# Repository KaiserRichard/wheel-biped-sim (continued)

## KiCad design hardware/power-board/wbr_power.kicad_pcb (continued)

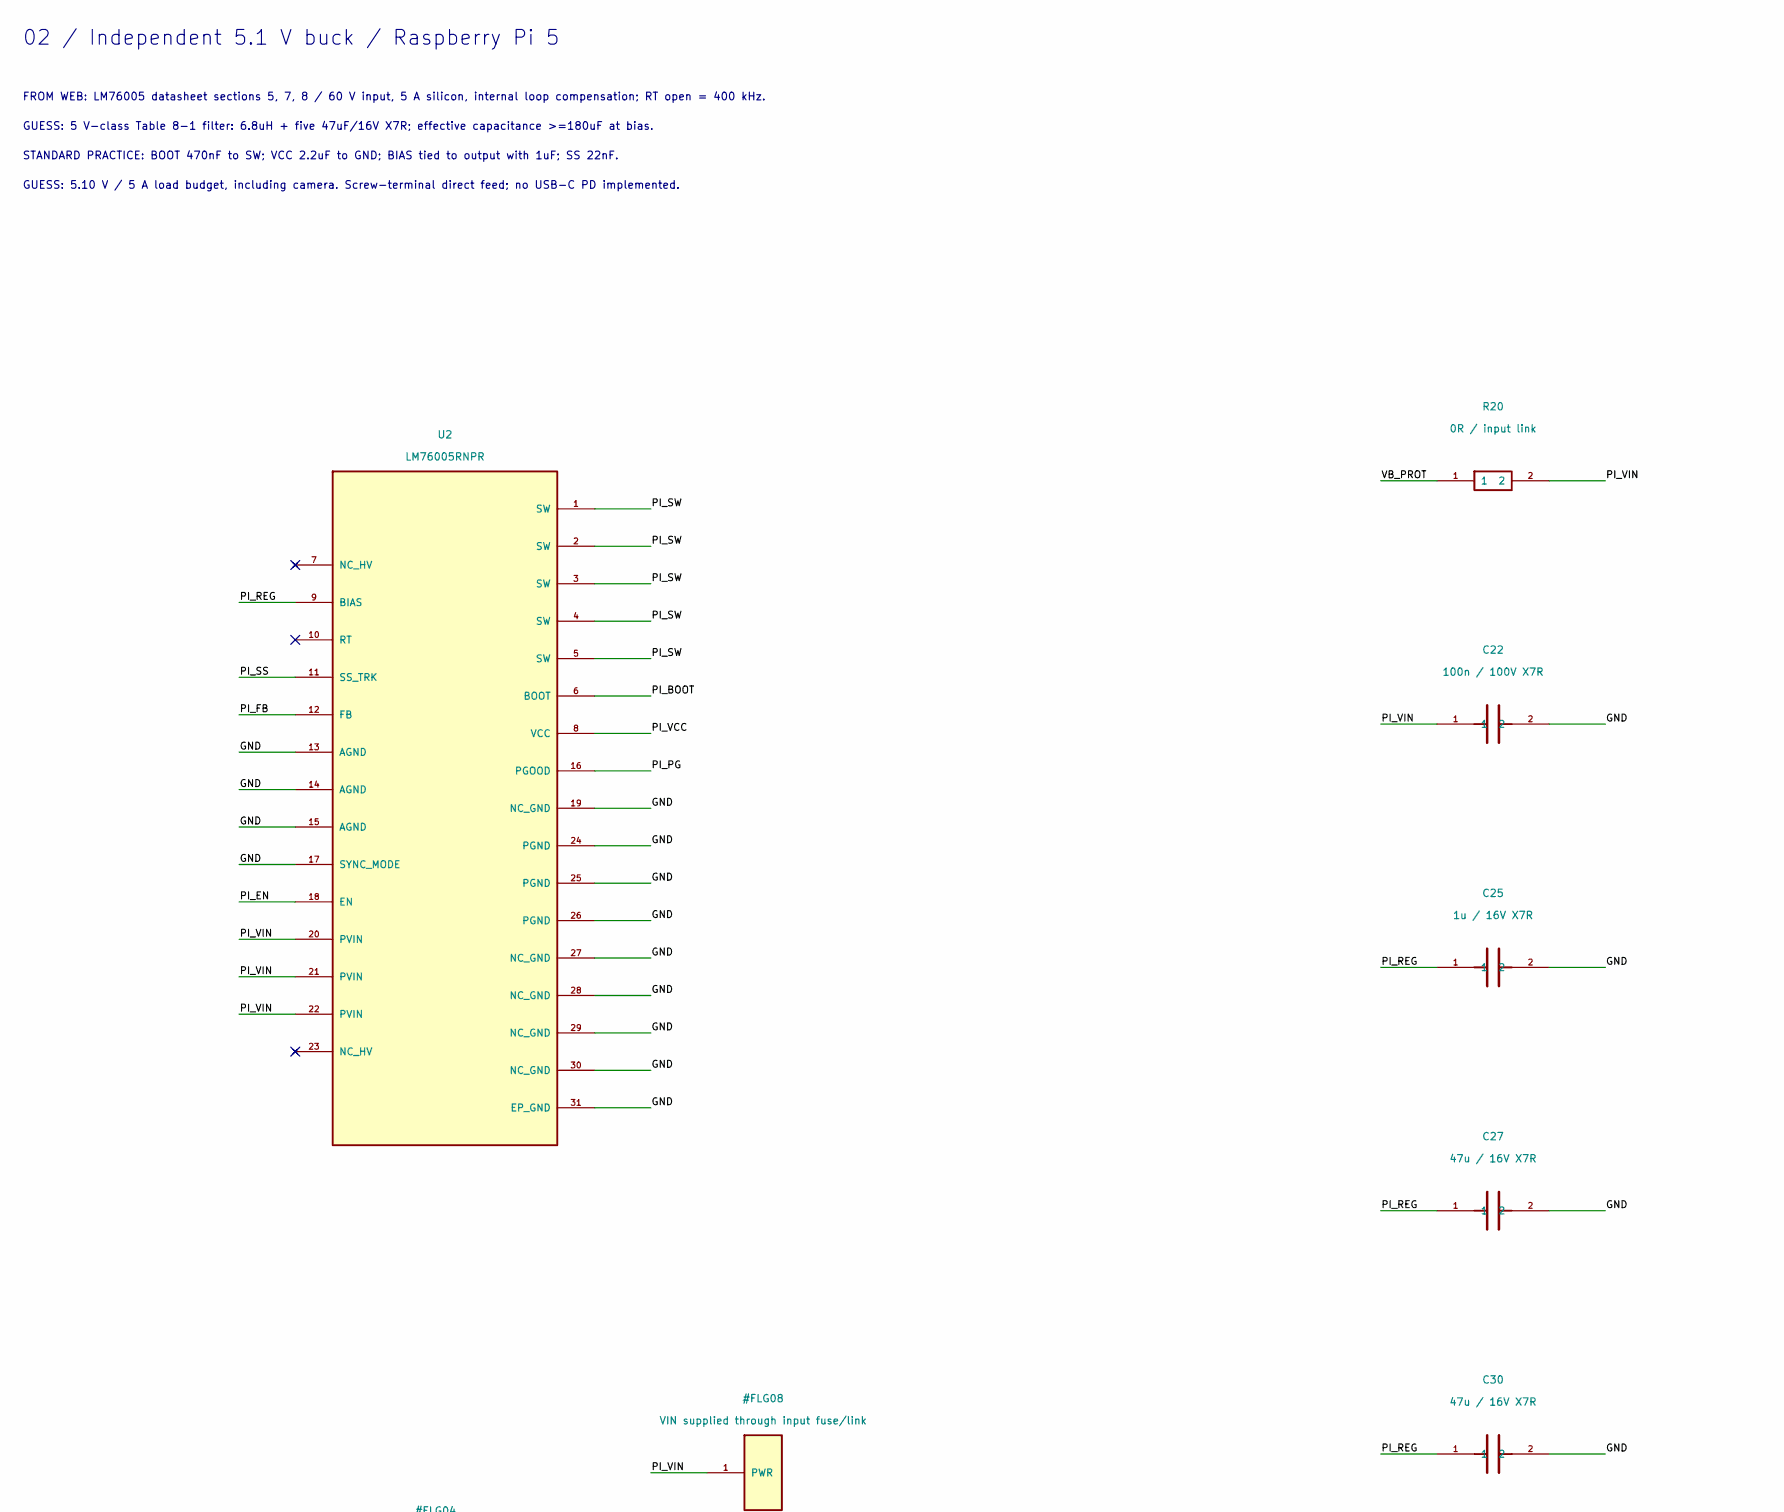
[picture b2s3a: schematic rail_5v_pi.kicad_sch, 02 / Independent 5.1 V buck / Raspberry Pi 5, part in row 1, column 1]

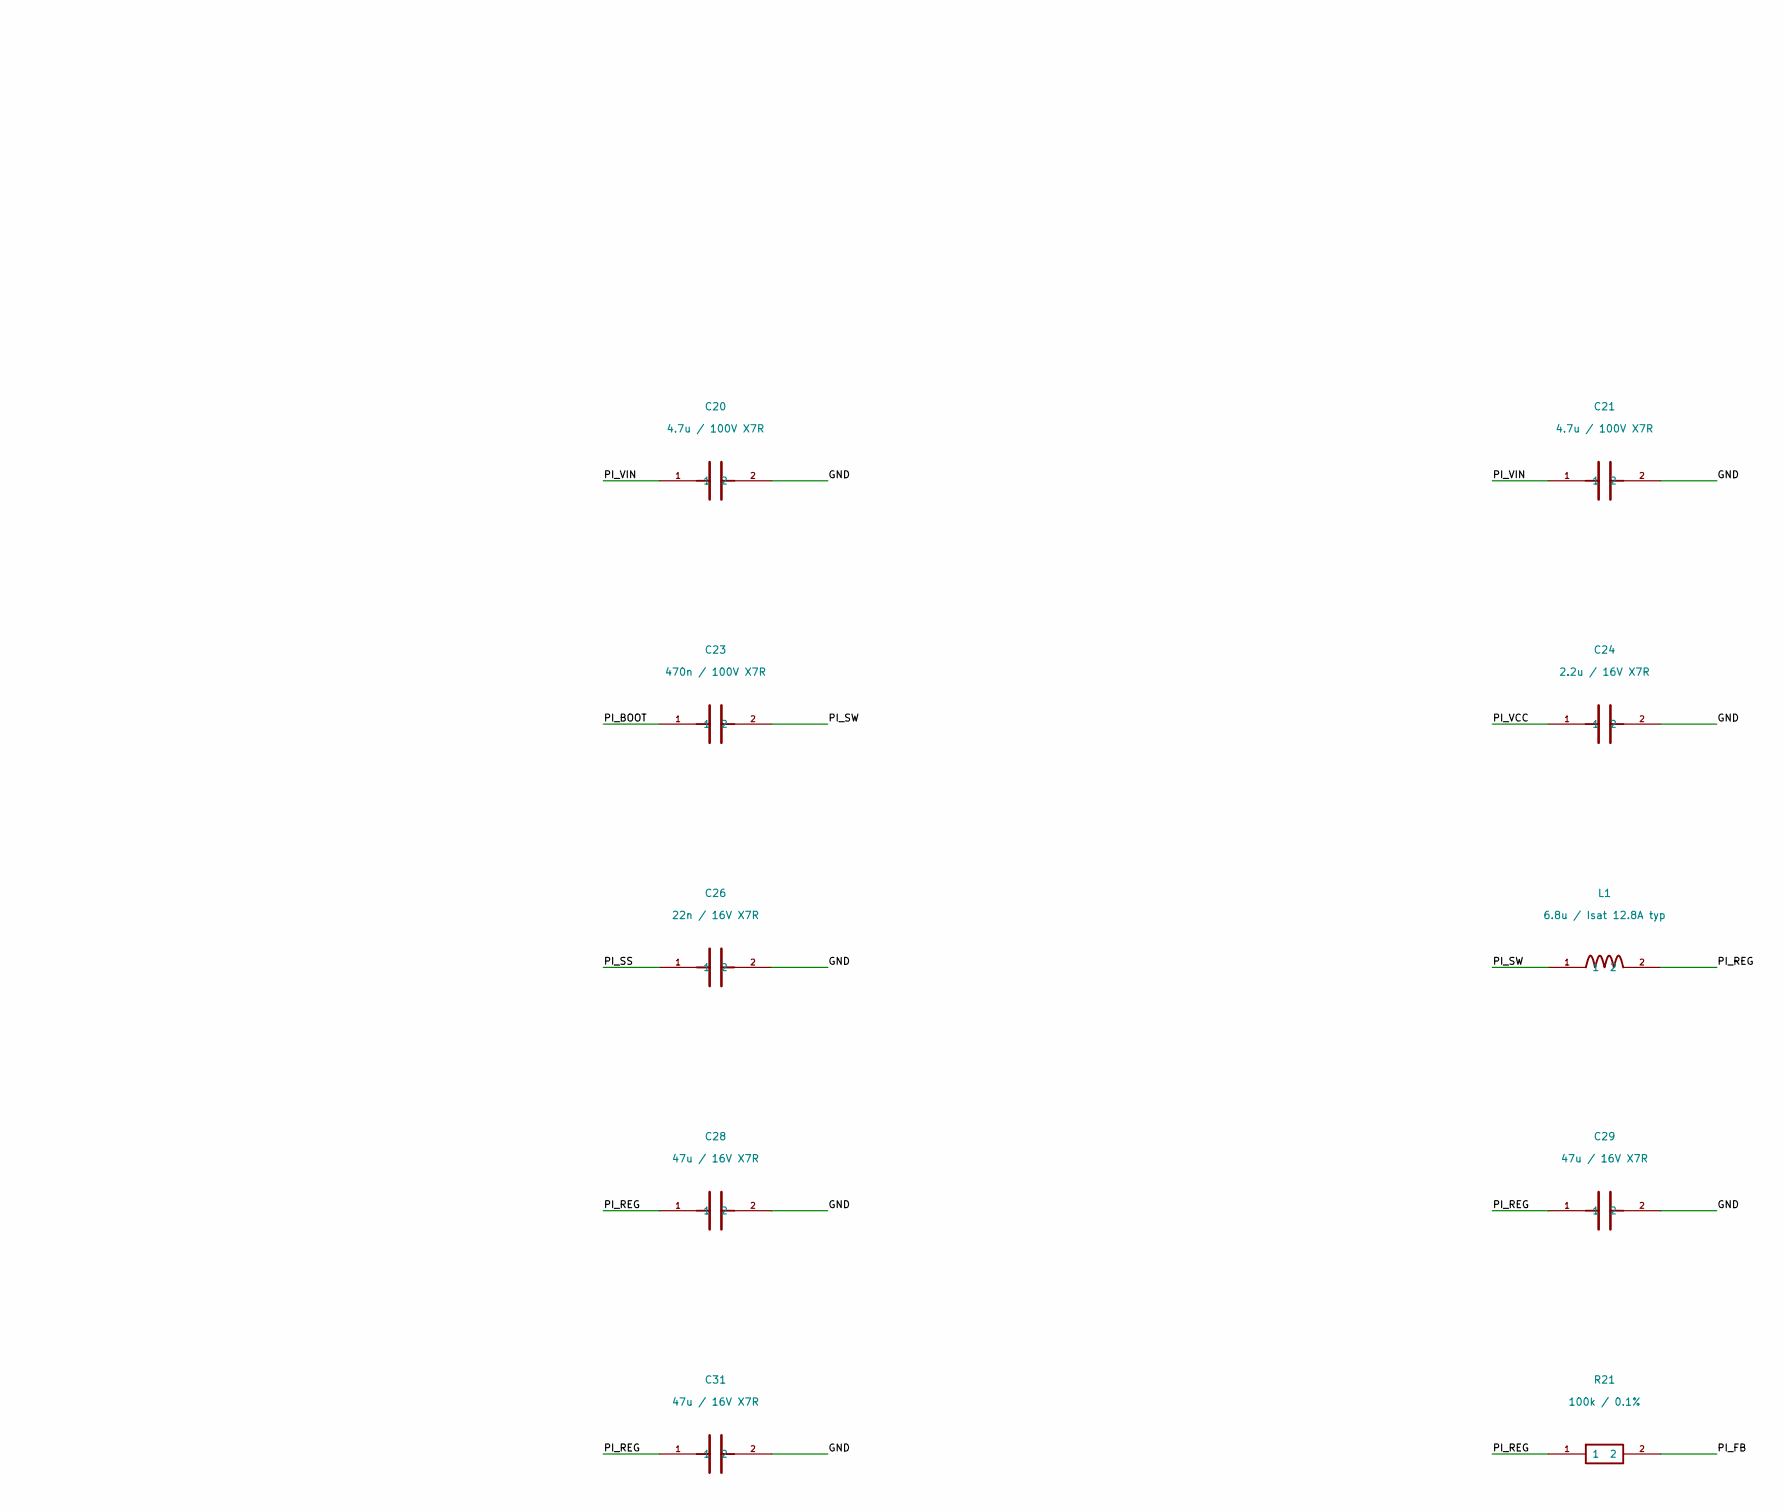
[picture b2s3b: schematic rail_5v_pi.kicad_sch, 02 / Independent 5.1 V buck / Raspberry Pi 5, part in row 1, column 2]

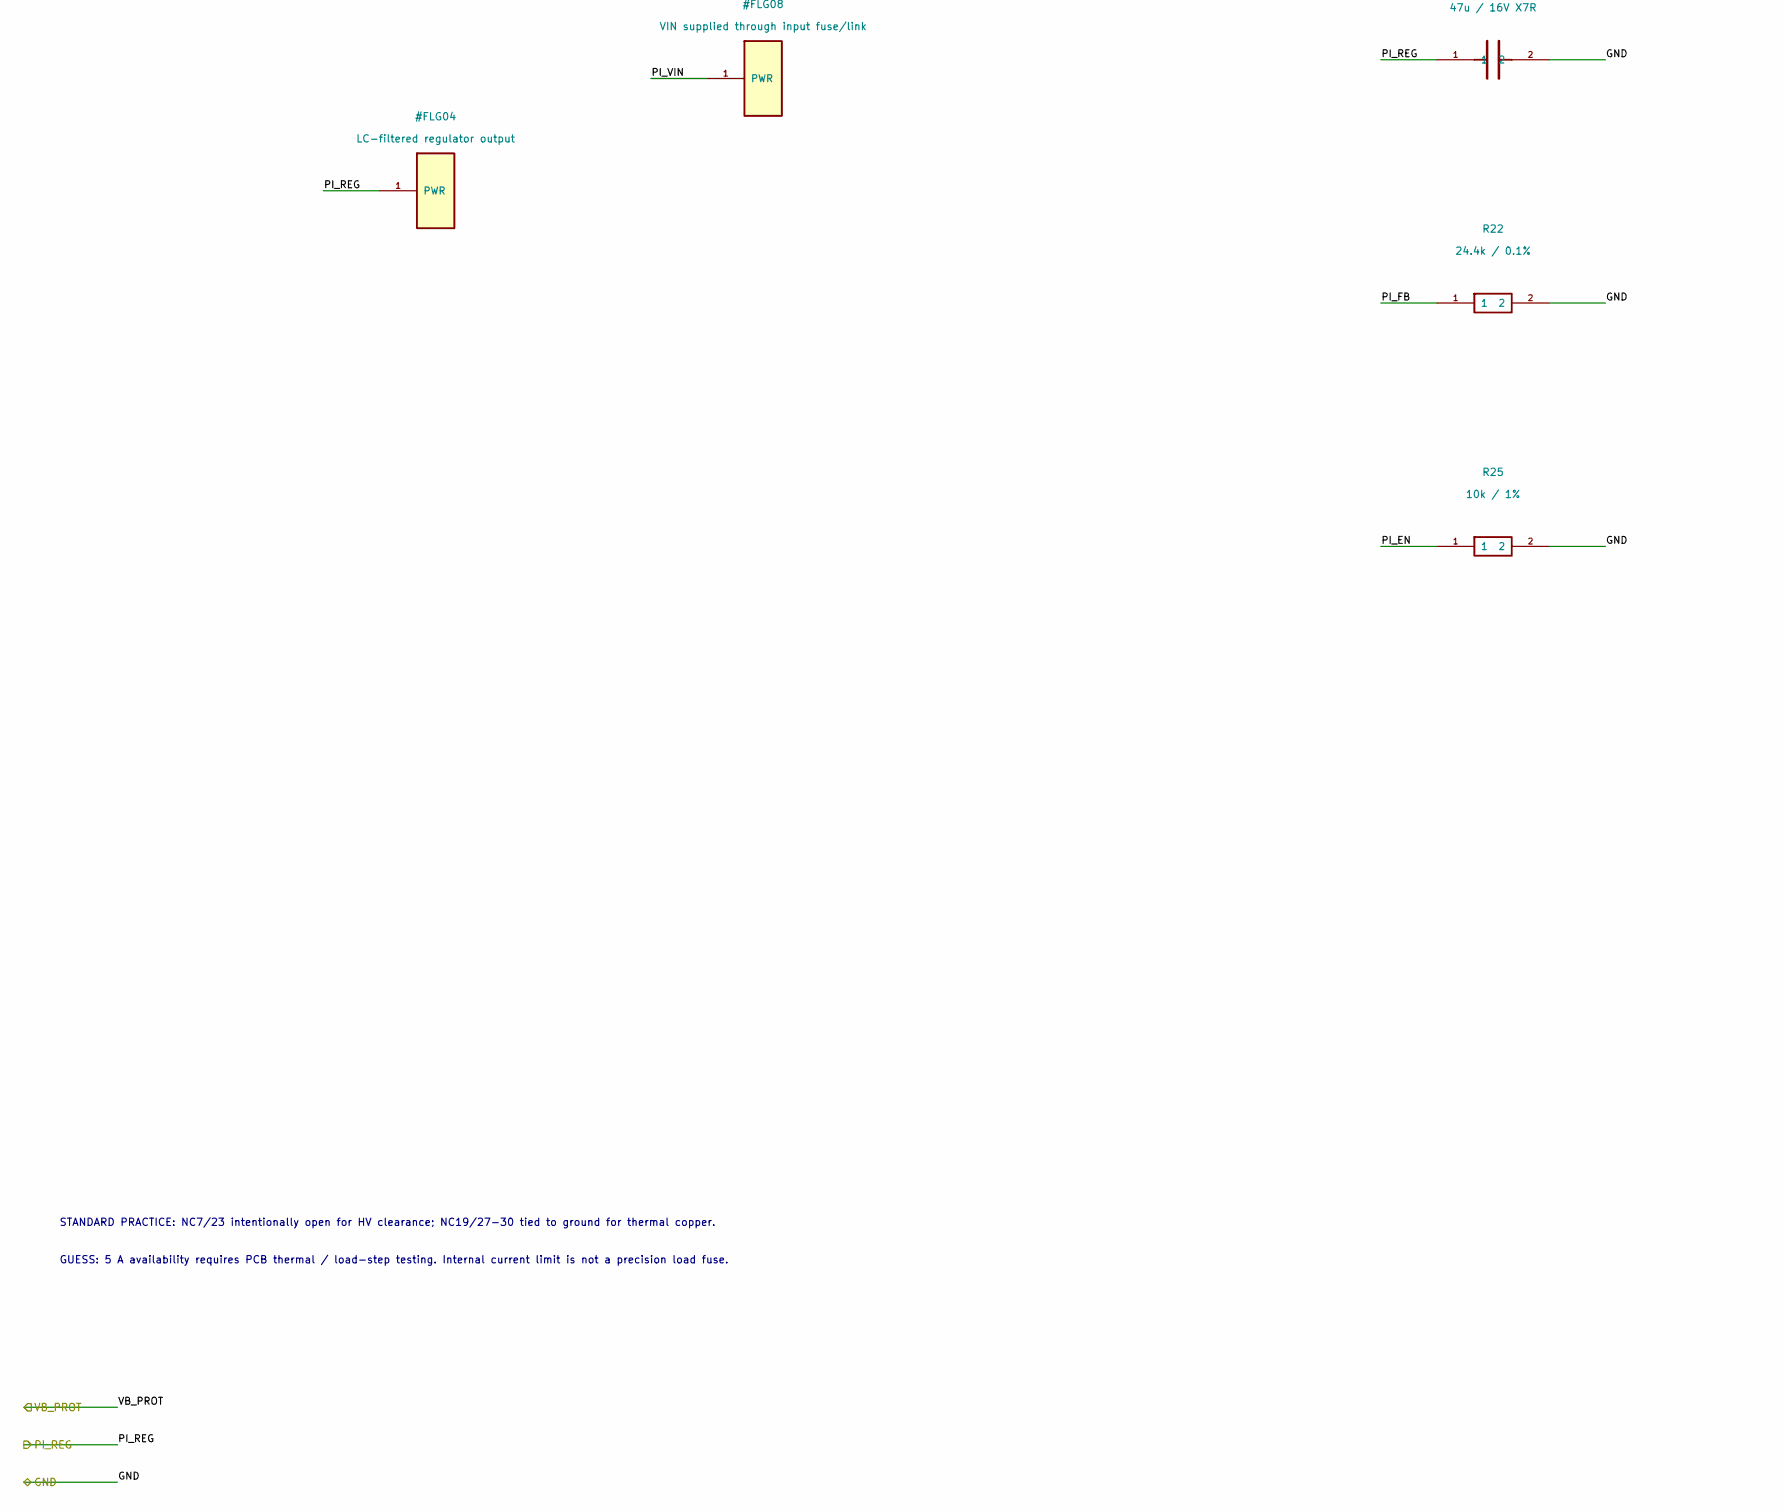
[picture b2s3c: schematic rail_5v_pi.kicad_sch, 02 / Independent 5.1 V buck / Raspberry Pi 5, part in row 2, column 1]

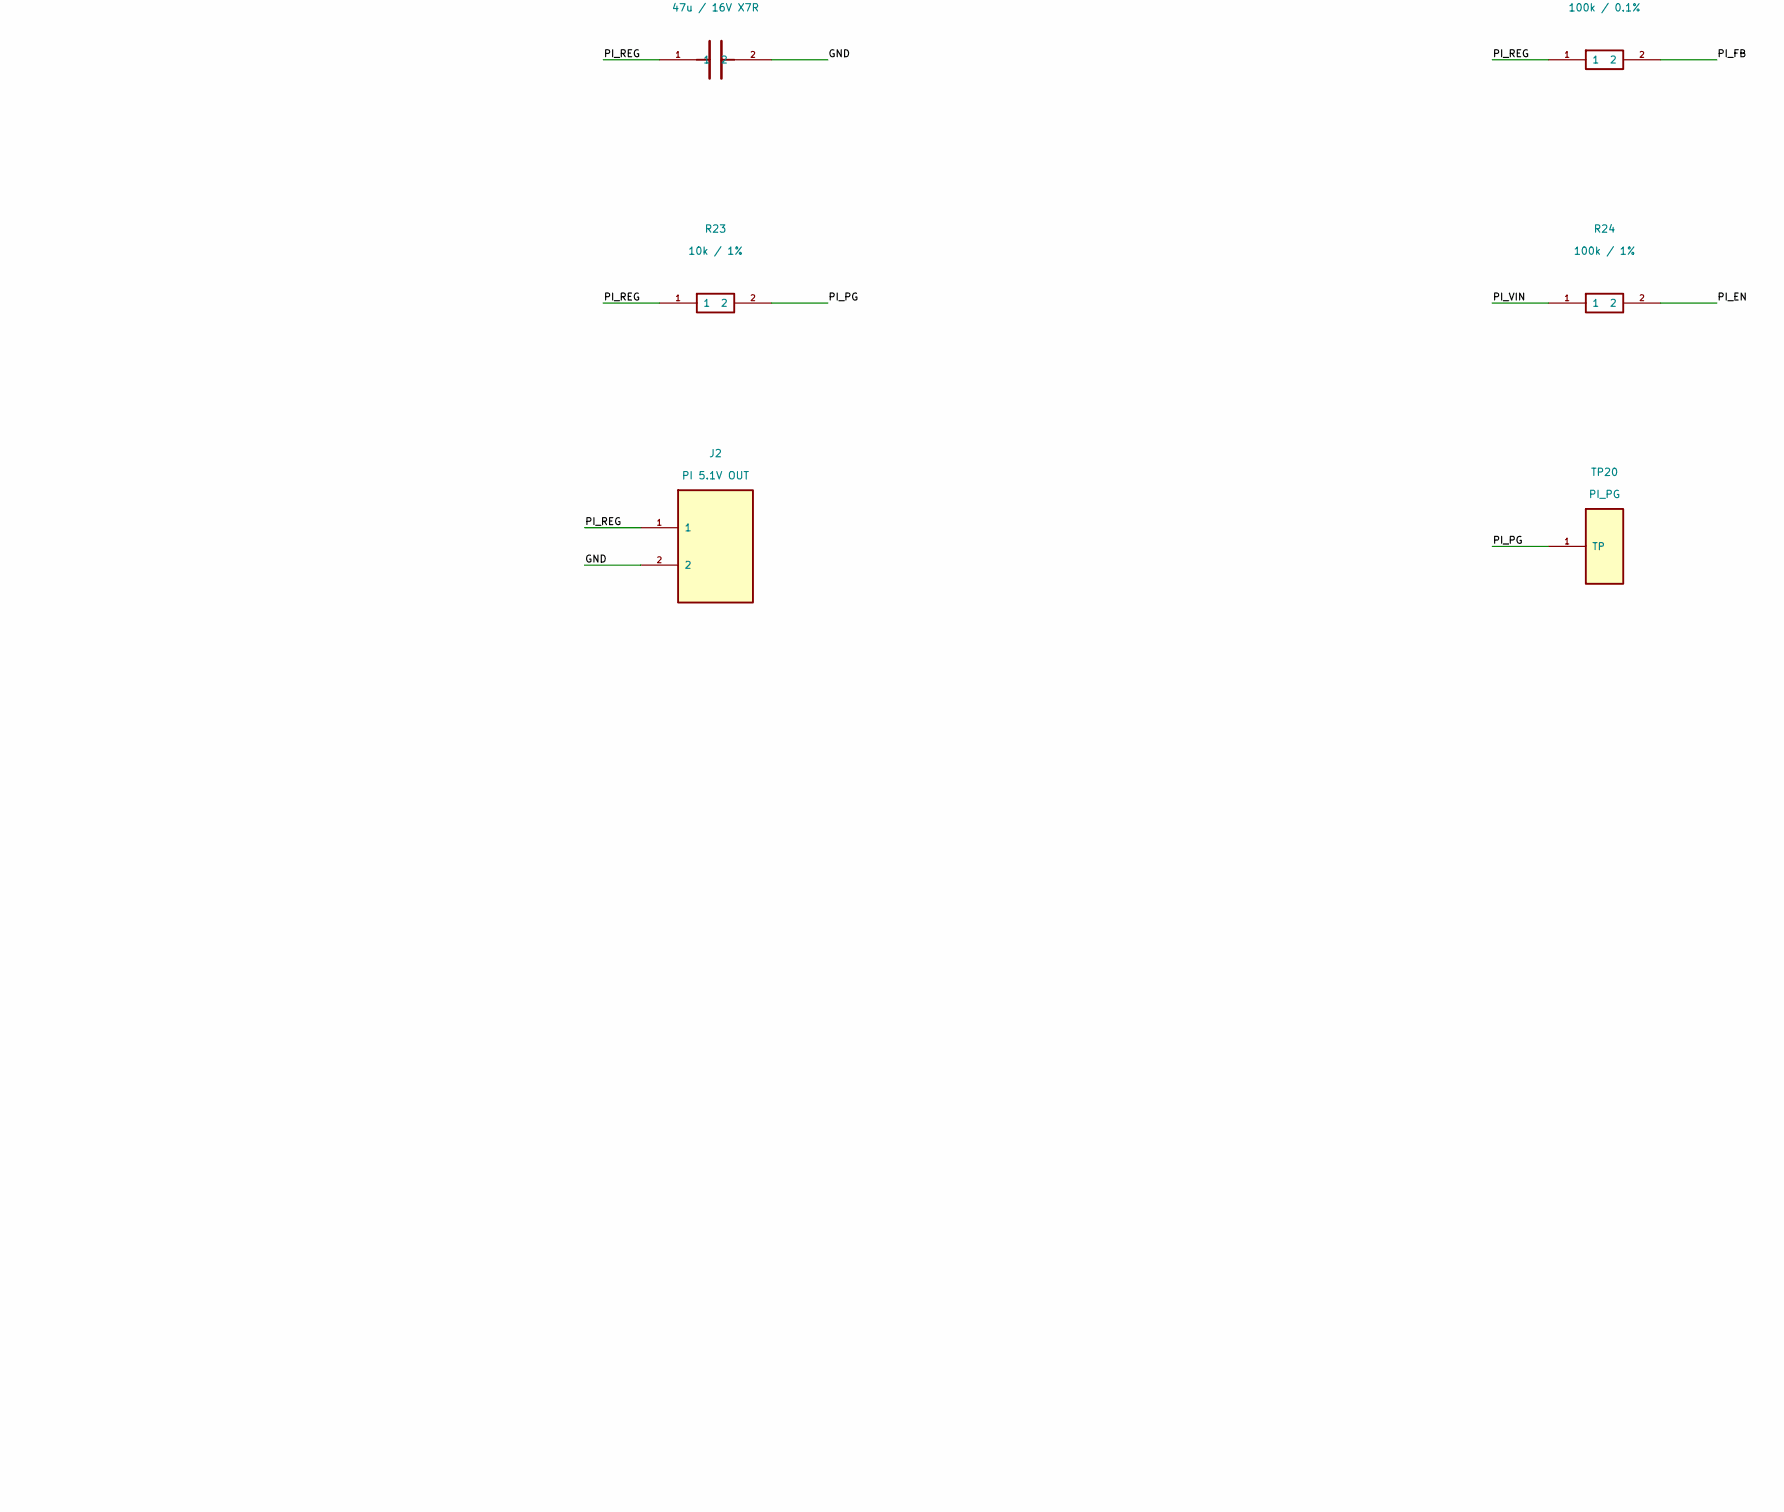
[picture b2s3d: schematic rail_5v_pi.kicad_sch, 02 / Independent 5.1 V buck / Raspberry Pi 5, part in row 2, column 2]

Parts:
C20, C21: 4.7u / 100V X7R; C_1210_3225Metric; Rating 100 V; verify effective capacitance; MPN 4.7u / 100V X7R
C22: 100n / 100V X7R; C_1210_3225Metric; Rating 100 V; MPN 100n / 100V X7R
C23: 470n / 100V X7R; C_1210_3225Metric; Rating 100 V; bootstrap floats at battery SW n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; MPN 470n / 100V X7R
C24: 2.2u / 16V X7R; C_0805_2012Metric; Rating 16 V; VCC decoupling; MPN 2.2u / 16V X7R
C25: 1u / 16V X7R; C_0805_2012Metric; Rating 16 V; BIAS decoupling; MPN 1u / 16V X7R
C26: 22n / 16V X7R; C_0805_2012Metric; Rating 16 V; ~11ms programmable soft-start; MPN 22n / 16V X7R
C27, C28, C29, C30, C31: 47u / 16V X7R; C_1210_3225Metric; Rating 16 V; five total >=180uF effective; MPN 47u / 16V X7R
J2: PI 5.1V OUT; TerminalBlock_Phoenix_MKDS-3-2-5.08_1x02_P5.08mm_Horizontal; Rating 250 V; >=8 A; MPN PI 5.1V OUT
L1: 6.8u / Isat 12.8A typ; L_Coilcraft_XAL7070-XXX; Rating 60 V operating; Irms 6.8 A / 20 C rise;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; MPN Coilcraft XAL7070-682MEC
R20: 0R / input link; R_2512_6332Metric; Rating 150 V / >=3 A; MPN 0R 2512
R21: 100k / 0.1%; R_0805_2012Metric; Rating 100 V; MPN 100k / 0.1%
R22: 24.4k / 0.1%; R_0805_2012Metric; Rating 100 V; MPN 24.4k / 0.1%
R23: 10k / 1%; R_0805_2012Metric; Rating 100 V; open-drain pull-up; MPN 10k / 1%
R24: 100k / 1%; R_1206_3216Metric; Rating 150 V; MPN 100k / 1%
R25: 10k / 1%; R_1206_3216Metric; Rating 150 V; MPN 10k / 1%
TP20: PI_PG; TestPoint_Pad_D2.0mm; Rating 5 V class PGOOD; not 3.3 V GPIO; MPN PI_PG
U2: LM76005RNPR; Texas_RNP0030B_WQFN-30-1EP_4x6mm_P0.5mm_EP1.8x4.5mm_Thermal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; Rating PVIN 60 V operating; 65 V absolute; 5 A; MPN LM76005RNPR

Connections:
/GND: C20.2, C21.2, C22.2, C24.2, C25.2, C26.2, C27.2, C28.2, C29.2, C30.2, C31.2, J2.2, R22.2, R25.2, U2.13 (AGND), U2.14 (AGND), U2.15 (AGND), U2.17 (SYNC_MODE), U2.19 (NC_GND), U2.24 (PGND), U2.25 (PGND), U2.26 (PGND), U2.27 (NC_GND), U2.28 (NC_GND), U2.29 (NC_GND), U2.30 (NC_GND), U2.31 (EP_GND); also elsewhere on the board
/PI_REG: C25.1, C27.1, C28.1, C29.1, C30.1, C31.1, J2.1, L1.2, R21.1, R23.1, U2.9 (BIAS); also elsewhere on the board
/VB_PROT: R20.1; also elsewhere on the board
/rail_5v_pi/PI_BOOT: C23.1, U2.6 (BOOT)
/rail_5v_pi/PI_EN: R24.2, R25.1, U2.18 (EN)
/rail_5v_pi/PI_FB: R21.2, R22.1, U2.12 (FB)
/rail_5v_pi/PI_PG: R23.2, TP20.1, U2.16 (PGOOD)
/rail_5v_pi/PI_SS: C26.1, U2.11 (SS_TRK)
/rail_5v_pi/PI_SW: C23.2, L1.1, U2.1 (SW), U2.2 (SW), U2.3 (SW), U2.4 (SW), U2.5 (SW)
/rail_5v_pi/PI_VCC: C24.1, U2.8 (VCC)
/rail_5v_pi/PI_VIN: C20.1, C21.1, C22.1, R20.2, R24.1, U2.20 (PVIN), U2.21 (PVIN), U2.22 (PVIN)

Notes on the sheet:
02 / Independent 5.1 V buck / Raspberry Pi 5
FROM WEB: LM76005 datasheet sections 5, 7, 8 / 60 V input, 5 A silicon, internal loop compensation; RT open = 400 kHz.
GUESS: 5 V-class Table 8-1 filter: 6.8uH + five 47uF/16V X7R; effective capacitance >=180uF at bias.
STANDARD PRACTICE: BOOT 470nF to SW; VCC 2.2uF to GND; BIAS tied to output with 1uF; SS 22nF.
GUESS: 5.10 V / 5 A load budget, including camera. Screw-terminal direct feed; no USB-C PD implemented.
STANDARD PRACTICE: NC7/23 intentionally open for HV clearance; NC19/27-30 tied to ground for thermal copper.
GUESS: 5 A availability requires PCB thermal / load-step testing. Internal current limit is not a precision load fuse.
